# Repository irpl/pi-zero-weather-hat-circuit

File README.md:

# Raspberry Pi Zero Weather Station HAT — Circuit

Design and manufacturing files for a custom Raspberry Pi Zero HAT that drives a weather station kit. Fabricated November 2020.

The board reads temperature and humidity from a **BME280**, and interfaces the kit's outdoor sensors — a wind vane, an anemometer, and a tipping-bucket rain gauge — through two RJ11/RJ12 jacks. Because the Pi has no analogue inputs, an **MCP3008** ADC on the Pi's SPI bus reads the wind vane's resistive output.

The board outline, mounting holes, and GPIO header come from [mikelawrence/RPi_Zero_pHat_Template](https://github.com/mikelawrence/RPi_Zero_pHat_Template); everything else is my own design.

**Firmware:** [pi-weather](https://github.com/irpl/pi-weather) — the Python that runs on the Pi.

| Gerber render — top | Gerber render — bottom |
|---|---|
|  |  |

## Manufacturing files

[`gerbers/`](gerbers/) holds the exact set sent to the fab: Gerbers for both copper layers, soldermask, silkscreen, board outline, plus the Excellon drill file. The board is reproducible from these as-is.

- Two-layer, 65 × 30 mm (Raspberry Pi HAT form factor)
- 87 drilled holes; 7 drill sizes from 0.40 mm to 3.25 mm
- Generated by KiCad 5.1.6

## Reconstructed schematic and layout

**The original KiCad project files were lost.** Only the Gerbers survived, so the schematic and board in [`reconstructed/`](reconstructed/) were rebuilt from them — see [`reconstructed/`](reconstructed/) for the scripts that did it.

*Full resolution: [`reconstructed/schematic.pdf`](reconstructed/schematic.pdf). The recovered layout, plotted from the reconstructed `.kicad_pcb`:*

The netlist is not a guess. Gerbers contain no connectivity, but the copper does: running a union-find over the pads and track segments (a plated hole ties the two layers together) recovers the netlist that was actually manufactured. That result is independently corroborated by the firmware — `wind_spd.py` uses `Button(5)` and the copper routes the Wind jack to GPIO5; `rain_fall.py` uses `Button(6)` and the copper routes RainFall to GPIO6; `wind_dir.py` reads `MCP3008(channel=0)` and the copper routes the vane to CH0.

### Circuit

- **MCP3008** on the Pi's hardware SPI — `SCLK`/`MISO`/`MOSI`/`CE0` on GPIO 11/9/10/8. `VDD` and `VREF` on 3V3.
- **Wind vane** — 3V3 feeds the vane through the Wind jack; the wiper returns to `CH0`, with **R1 (5 kΩ)** to ground forming the divider the ADC reads.
- **Anemometer** — reed switch to **GPIO5**.
- **Rain gauge** — reed switch to **GPIO6**.
- **BME280** — I²C on `GPIO2 (SDA)` / `GPIO3 (SCL)`, address `0x77`.

### Jack pinout

Both jacks use the standard staggered modular footprint: pin numbers advance across the connector, with odd pins in one row and even pins in the other.

| Jack | Pin 2 | Pin 3 | Pin 4 | Pin 5 |
|---|---|---|---|---|
| **Wind** (6P4C) | vane wiper → `CH0` | anemometer → GPIO5 | GND | +3V3 |
| **RainFall** (6P2C) | — | rain gauge → GPIO6 | GND | — |

The reed switches in the anemometer and rain gauge simply short their signal pin to GND; `gpiozero`'s `Button()` enables the Pi's internal pull-ups, so no pull-up resistors are fitted on the board.

**R1 = 5 kΩ.** Component values are not in Gerber data, but this one is pinned down two ways: the colour bands on the fitted resistor read green-black-red, and the empirical voltage table in [`wind_dir.py`](https://github.com/irpl/pi-weather/blob/main/src/wind_dir.py) matches a 5 kΩ divider against the standard vane resistances at every point — a 1 kΩ vane arm gives 3.3 × 5/6 = 2.75 V, and 2.75 is exactly what the table records for 90°.

### Fidelity of the reconstructed board

The `.kicad_pcb` is not a bare tracing: pads are grouped into components with reference designators and pin numbers, and the recovered netlist is applied to pads, tracks and vias. It opens with a working ratsnest and passes connectivity DRC. Contents: 6 components (77 pads), 8 unplated mounting holes, 2 vias, 100 tracks, 11 nets — 87 drilled holes in total, matching the drill file exactly.

Copper geometry was checked against the source Gerbers by re-plotting from the reconstruction and comparing: **0.000 mm difference in total track length on both layers**, pad positions within 1.6 µm (coordinate rounding in the 2020 files), and identical apertures and drill tools.

Two deliberate departures from the artwork, both improvements rather than losses:

- **The board outline is not drawn onto the copper layers.** KiCad 5 plotted Edge.Cuts onto F.Cu and B.Cu as well; that stroke is a plot artifact, not copper, so it is kept on Edge.Cuts only. Copying it into copper would put a trace exactly on the cut line.
- **Mounting-hole mask openings are taken from the mask Gerbers**, preserving the 6.2 mm soldermask keep-out rings around the RJ-jack mounting holes.

DRC reports 4 copper-to-edge-clearance and 1 soldermask-bridge violation. All five are faithful to the original artwork, not artefacts of the conversion: the 2020 design runs copper right up to the board edge and uses generous mask expansion on the 0.1″ headers. Two "unconnected" items are also expected — the +3V3 and GND rails each exist as two separate copper islands on the HAT (Pi pins 1/17 and 9/39) and are only bonded once the board is seated on the Pi.

One quirk faithfully preserved: a 0.66 mm dangling stub on GPIO25 (J1 pin 22), left over in the original copper and connected to nothing.

### What could not be recovered

Gerbers carry geometry, not design intent. These are stated rather than invented:

- **Component values**, other than R1 (5 kΩ, established above). Gerber data has no values, so no BOM can be generated from these files.
- **Library footprints.** Pads carry recovered geometry — correct size, shape, position and drill — but they are not linked to library footprints, so there is no 3D model or pick-and-place data.
- **Silkscreen text** is line art in the Gerbers, so in the reconstructed board it is strokes rather than editable text.

It is a re-spinnable, netlisted board — but it is a reconstruction, not the original project.

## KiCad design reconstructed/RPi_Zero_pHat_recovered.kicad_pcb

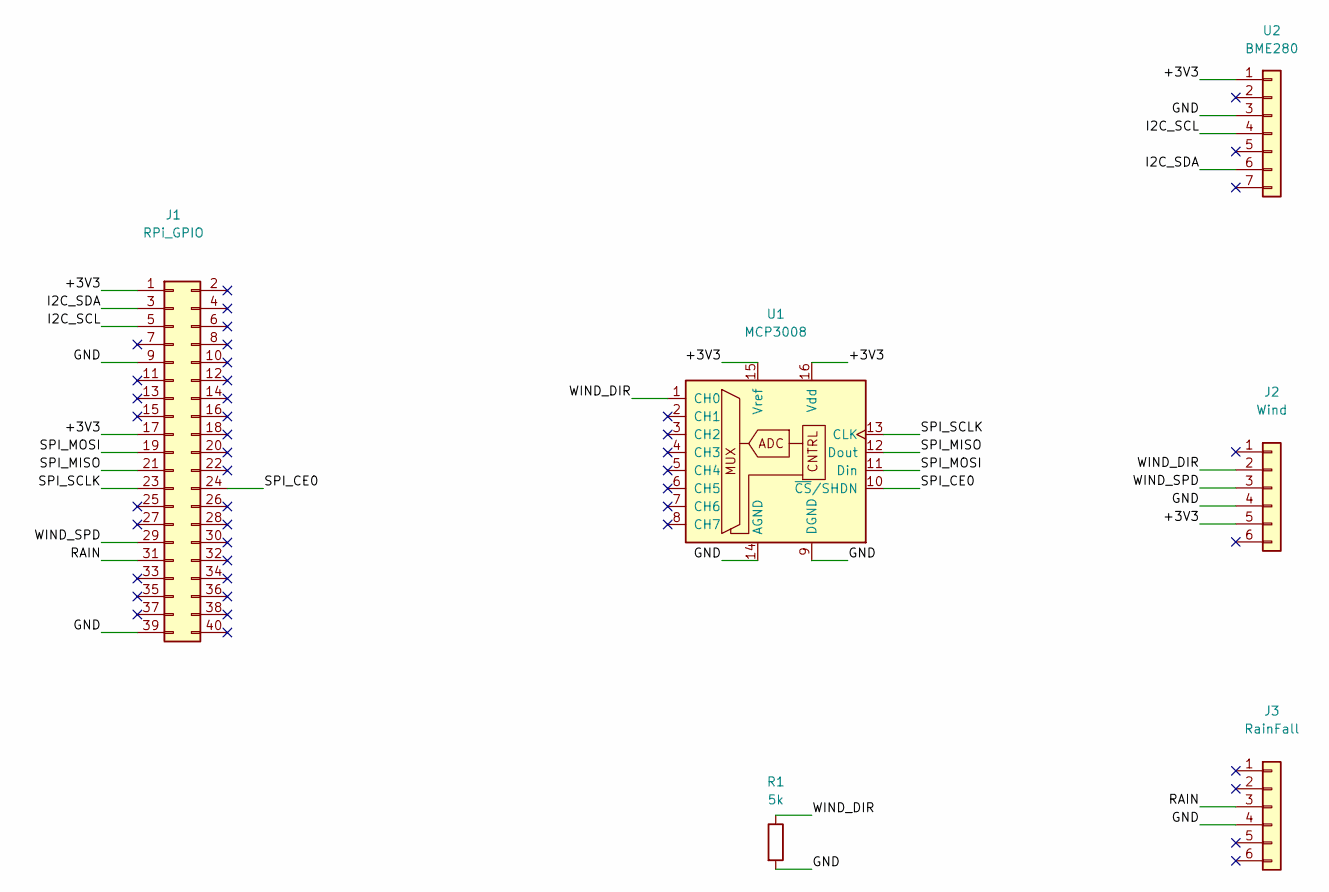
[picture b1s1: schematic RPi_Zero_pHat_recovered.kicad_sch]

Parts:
J1: RPi_GPIO
J2: Wind
J3: RainFall
R1: 5k
U1: MCP3008
U2: BME280

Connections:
+3V3: J1.1, J1.17, J2.5, U1.15 (Vref), U1.16 (Vdd), U2.1
GND: J1.9, J1.39, J2.4, J3.4, R1.2, U1.9 (DGND), U1.14 (AGND), U2.3
I2C_SCL: J1.5, U2.4
I2C_SDA: J1.3, U2.6
RAIN: J1.31, J3.3
SPI_CE0: J1.24, U1.10 (~CS/SHDN)
SPI_MISO: J1.21, U1.12 (Dout)
SPI_MOSI: J1.19, U1.11 (Din)
SPI_SCLK: J1.23, U1.13 (CLK)
WIND_DIR: J2.2, R1.1, U1.1 (CH0)
WIND_SPD: J1.29, J2.3

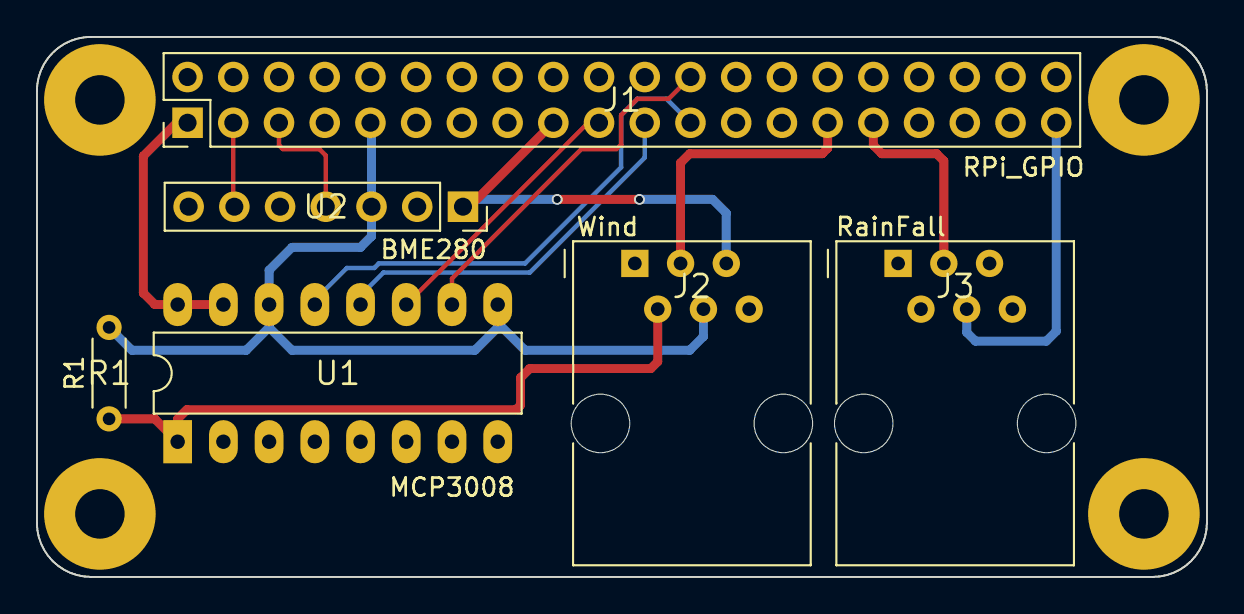
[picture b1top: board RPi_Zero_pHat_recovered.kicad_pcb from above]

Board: 2 copper layers, 65.0 x 30.0 mm, 14 parts (0 on the bottom side), 11 nets.

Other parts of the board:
H1, H2, H3, H4, H5, H6, H7, H8: (no value)
